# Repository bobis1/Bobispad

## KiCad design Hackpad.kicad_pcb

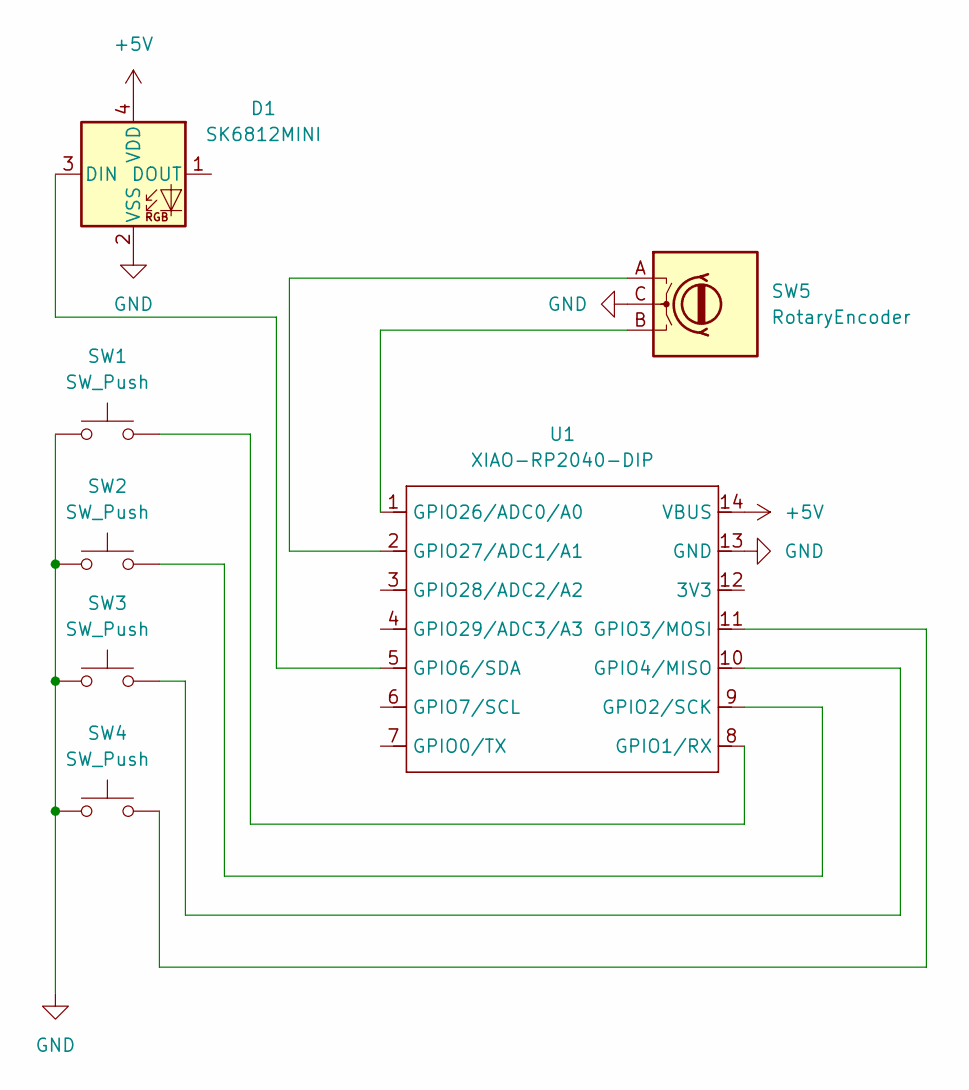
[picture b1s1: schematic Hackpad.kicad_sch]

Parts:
D1: SK6812MINI; LED_SK6812MINI_PLCC4_3.5x3.5mm_P1.75mm
SW1, SW2, SW3, SW4: SW_Push; SW_Cherry_MX_1.00u_PCB
SW5: RotaryEncoder; RotaryEncoder_Alps_EC11E-Switch_Vertical_H20mm
U1: XIAO-RP2040-DIP

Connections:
+5V: D1.4 (VDD), U1.14 (VBUS)
GND: D1.2 (VSS), SW1.1, SW2.1, SW3.1, SW4.1, SW5.C, U1.13 (GND)
unnamed: D1.3 (DIN), U1.5 (GPIO6/SDA)
unnamed: SW1.2, U1.8 (GPIO1/RX)
unnamed: SW2.2, U1.9 (GPIO2/SCK)
unnamed: SW4.2, U1.11 (GPIO3/MOSI)
unnamed: SW3.2, U1.10 (GPIO4/MISO)
unnamed: SW5.B, U1.1 (GPIO26/ADC0/A0)
unnamed: SW5.A, U1.2 (GPIO27/ADC1/A1)

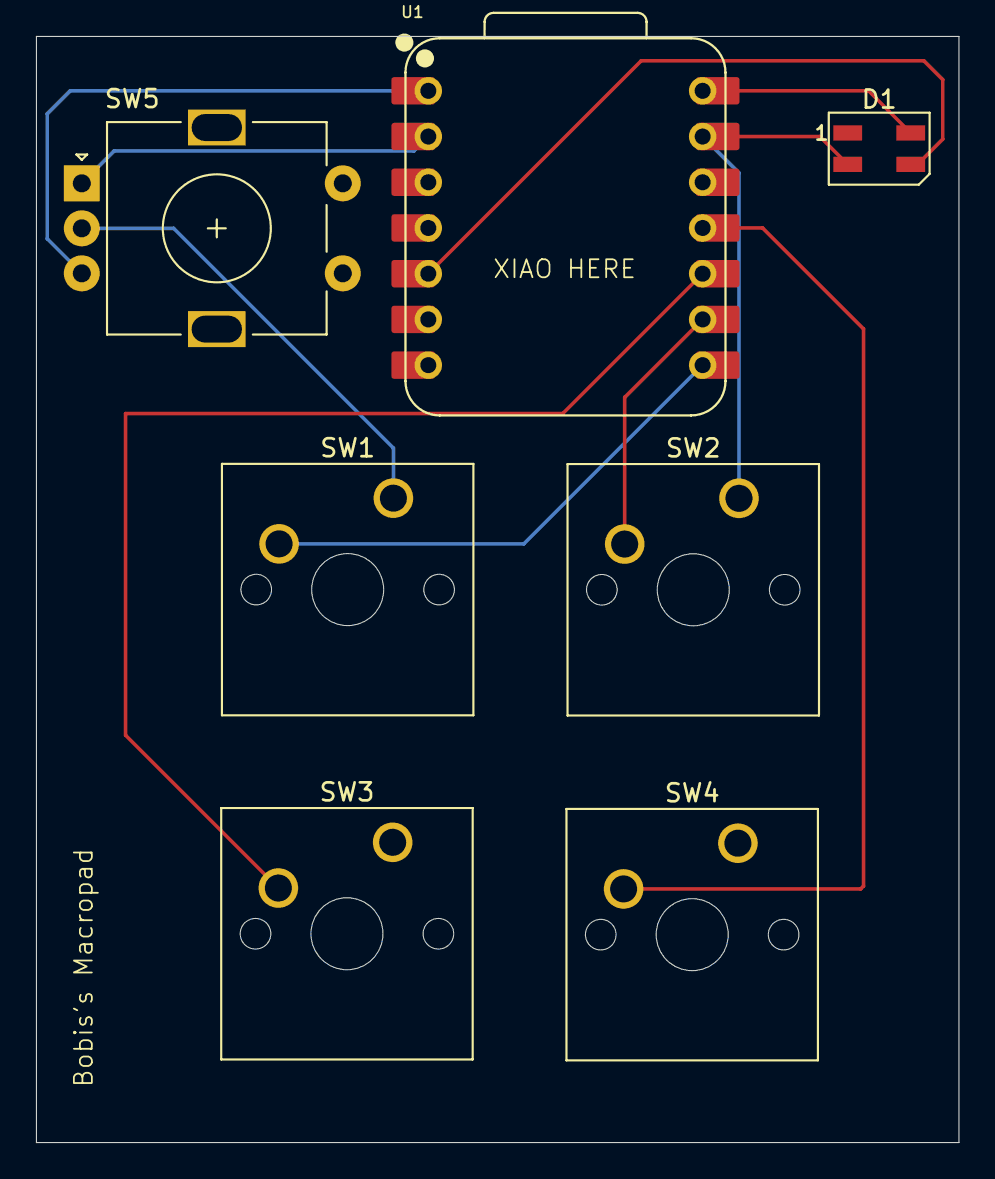
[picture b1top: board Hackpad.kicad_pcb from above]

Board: 2 copper layers, 51.2 x 61.5 mm, 7 parts (0 on the bottom side), 9 nets.

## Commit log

2025-12-03 Initalized the marcropad
2025-12-07 Added PCB design
2025-12-07 Added the case model and the firmware base
